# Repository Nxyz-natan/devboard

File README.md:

# devboard
A compact ESP32 development board with onboard 2" ST7789 display, USB-C, LiPo charging via IP5306, GPIO headers, status LEDs, and CH340C for easy programming. Built on the ESP32-WROOM-32 for WiFi and Bluetooth.

my finished pcb

my finished schematics

## Bill of Materials

| Name | Purpose | Qty | Total Cost (USD) | Distributor | Link |
|------|---------|-----|-----------------|-------------|------|
| PCB | PCB | 1 | $1.50 | JLCPCB | - |
| Mini Hotplate | Soldering | 1 | $13.26 | Amazon | - |
| LiPo Battery 1000mAh JST | Battery | 1 | $7.83 | Amazon | - |
| LCSC ST7789 2.0inch Screen | Screen | 1 | $7.67 | LCSC | [link](https://www.lcsc.com/product-detail/C53184555.html) |
| ESP32-WROOM-32-N4 | MCU | 1 | $4.29 | LCSC | [link](https://www.lcsc.com/product-detail/C82899.html) |
| K2-1102SP Push Button | Button | 10 | $0.45 | LCSC | [link](https://www.lcsc.com/product-detail/C127509.html) |
| YLED0402Y LED Yellow | LED | 50 | $0.69 | LCSC | [link](https://www.lcsc.com/product-detail/C20608782.html) |
| EVERLIGHT Green LED | LED | 10 | $0.43 | LCSC | [link](https://www.lcsc.com/product-detail/C74338.html) |
| NATIONSTAR Red LED | LED | 50 | $0.67 | LCSC | [link](https://www.lcsc.com/product-detail/C84256.html) |
| YAGEO 100R 0402 | Resistor | 100 | $0.09 | LCSC | [link](https://www.lcsc.com/product-detail/C106232.html) |
| UNI-ROYAL 1K 0402 | Resistor | 100 | $0.07 | LCSC | [link](https://www.lcsc.com/product-detail/C11702.html) |
| YAGEO 10K 0603 | Resistor | 100 | $0.15 | LCSC | [link](https://www.lcsc.com/product-detail/C98220.html) |
| YAGEO 5.1K 0402 | Resistor | 100 | $0.09 | LCSC | [link](https://www.lcsc.com/product-detail/C105872.html) |
| Samsung 100uF 1206 Cap | Capacitor | 10 | $0.61 | LCSC | [link](https://www.lcsc.com/product-detail/C15008.html) |
| YAGEO 100nF 0402 Cap | Capacitor | 100 | $0.10 | LCSC | [link](https://www.lcsc.com/product-detail/C60474.html) |
| Samsung 10uF 0603 Cap | Capacitor | 50 | $0.40 | LCSC | [link](https://www.lcsc.com/product-detail/C19702.html) |
| Pin Header 1x20 2.54mm | Header | 50 | $0.72 | LCSC | [link](https://www.lcsc.com/product-detail/C50981.html) |
| Pin Header 1x2 2.54mm | Header | 10 | $0.61 | LCSC | [link](https://www.lcsc.com/product-detail/C49661.html) |
| USB-C Receptacle 14P | Connector | 5 | $0.85 | LCSC | [link](https://www.lcsc.com/product-detail/C165948.html) |
| MMBT3904 NPN Transistor | Transistor | 50 | $0.49 | LCSC | [link](https://www.lcsc.com/product-detail/C20526.html) |
| 2N7002 MOSFET | MOSFET | 50 | $0.67 | LCSC | [link](https://www.lcsc.com/product-detail/C8545.html) |
| IP5306 Battery IC | Power | 5 | $1.41 | LCSC | [link](https://www.lcsc.com/product-detail/C181692.html) |
| AMS1117-3.3 LDO | Regulator | 5 | $1.13 | LCSC | [link](https://www.lcsc.com/product-detail/C6186.html) |
| CH340C USB-UART | USB-UART | 1 | $0.58 | LCSC | [link](https://www.lcsc.com/product-detail/C84681.html) |
| JST B2B-PH-K-S(LF)(SN) | JST PH 2.0mm 2pin vertical connector | 20 | $0.67 | LCSC | [link](https://www.lcsc.com/product-detail/C131337.html?s_z=n_JST%2520PH%25202.0mm%25202pin%2520vertical%2520connector&spm=wm.ssy.bg.0.xh&lcsc_vid=ElILAgAEQVUPAgEDTldfUFVVQgMPUQdXRlUMVFMHQVcxVlNRQVBdVFFWQVVdUzsOAxUeFF5JWBYZEEoKFBINSQcJGk4dAgUUFAk%3D) |
soldering paste  soldering   5.09$
soldering tweeters	placing down components	-	$5.89	-	aliexpress

total with shipping and tax: $74.93 usd

finished soldering

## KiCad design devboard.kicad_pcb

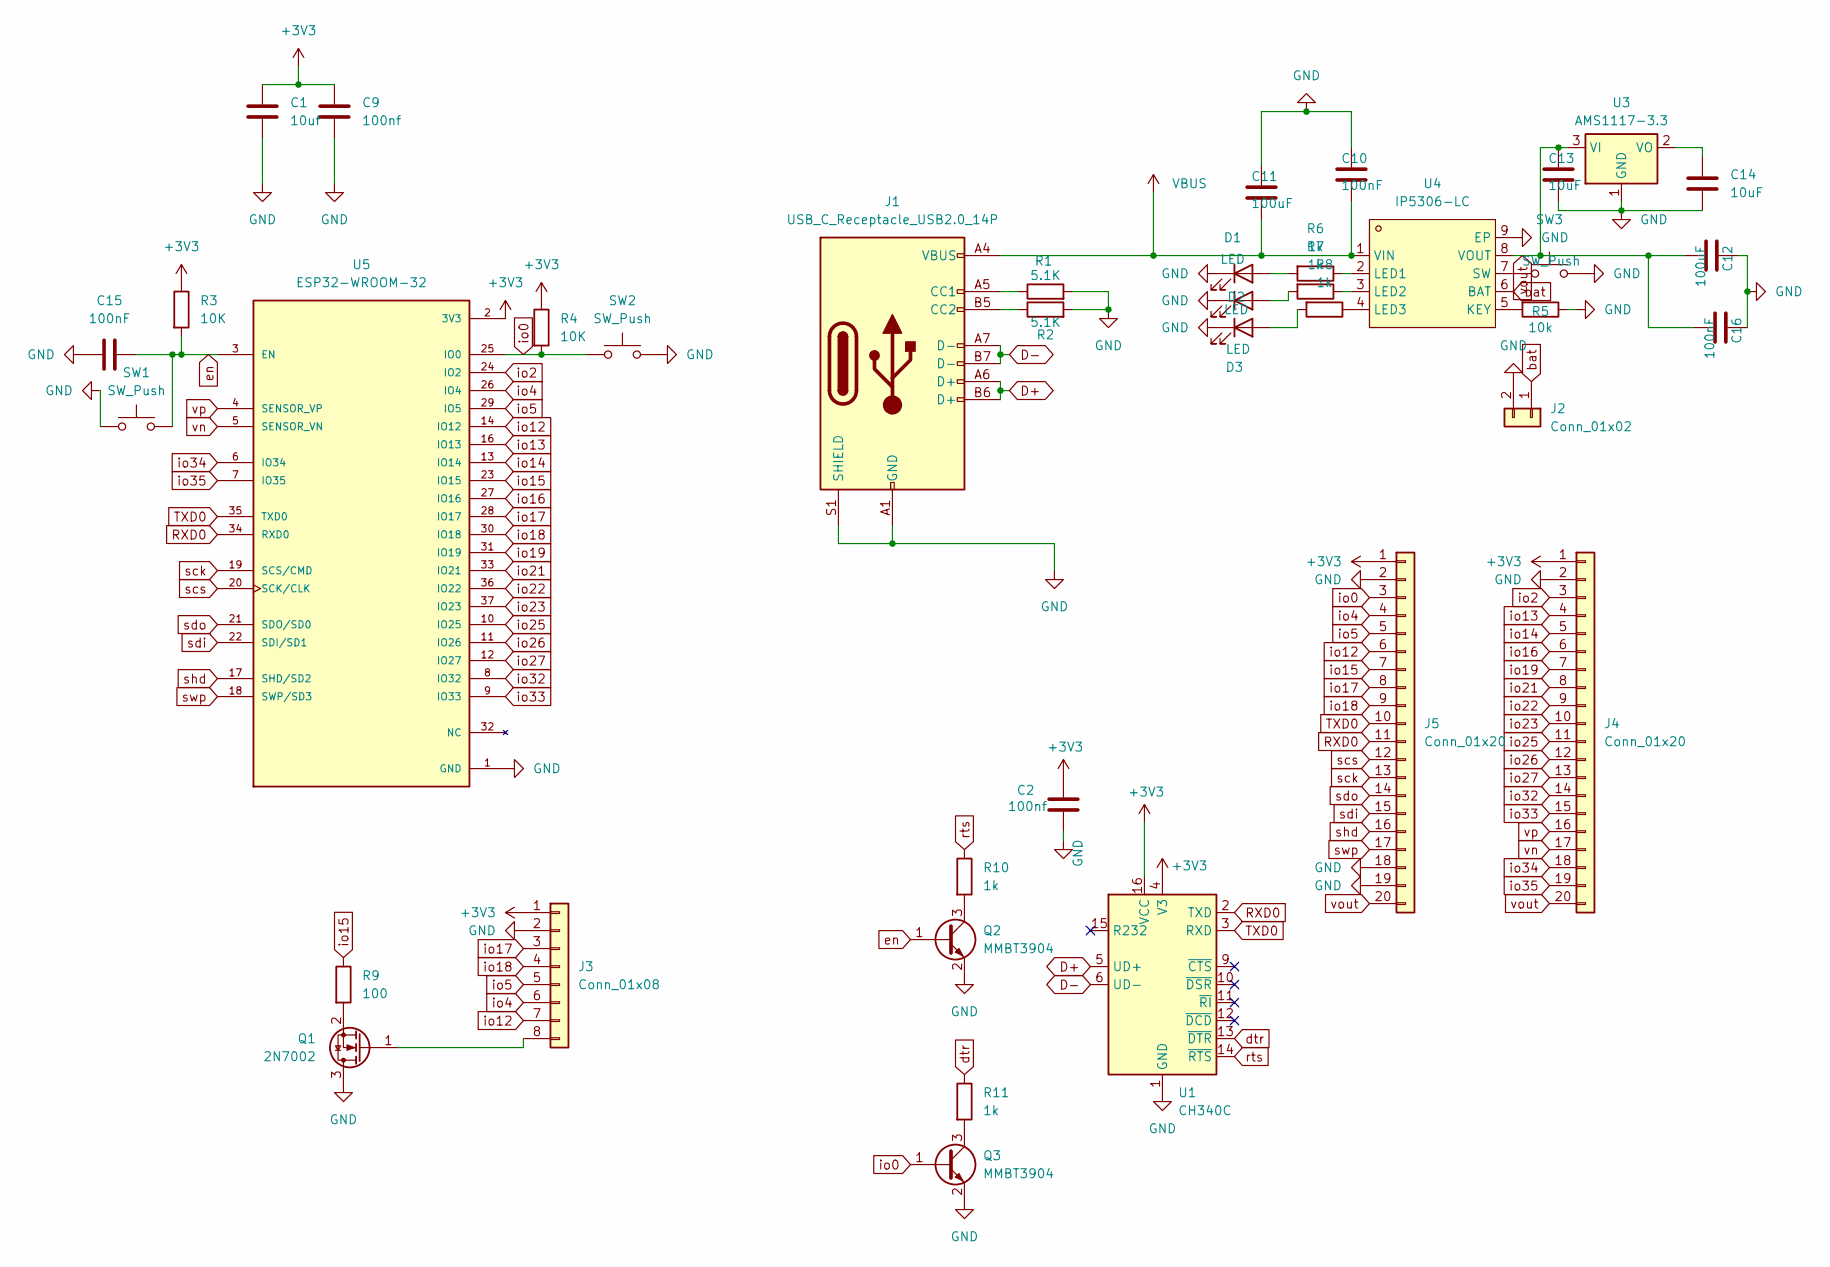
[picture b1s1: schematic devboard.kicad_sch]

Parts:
C1: 10uf; C_0603_1608Metric
C2, C9: 100nf; C_0402_1005Metric
C10, C16: 100nF; C_0603_1608Metric
C11, C12: 100uF; C_1206_3216Metric
C13, C14: 10uF; C_0603_1608Metric
C15: 100nF; C_0402_1005Metric
D1, D2, D3: LED; LED_0402_1005Metric
J1: USB_C_Receptacle_USB2.0_14P; USB_C_Receptacle_HRO_TYPE-C-31-M-12
J2: Conn_01x02; JST_PH_S2B-PH-K_1x02_P2.00mm_Horizontal
J3: Conn_01x08; PinHeader_1x08_P2.54mm_Vertical
J4, J5: Conn_01x20; PinHeader_1x20_P2.54mm_Vertical
Q1: 2N7002; SOT-23
Q2, Q3: MMBT3904; SOT-23
R1, R2: 5.1K; R_0402_1005Metric
R3, R4: 10K; R_0402_1005Metric
R5: 10k; R_0402_1005Metric
R6, R7, R8, R10, R11: 1k; R_0402_1005Metric
R9: 100; R_0402_1005Metric
SW1, SW2, SW3: SW_Push; SW_SPST_TL3342
U1: CH340C; SOIC-16_3.9x9.9mm_P1.27mm
U3: AMS1117-3.3; SOT-223-3_TabPin2
U4: IP5306-LC; ESOP-8_L4.9-W3.9-P1.27-LS6.0-BL-EP; MPN IP5306-LC; LCSC Part C605440
U5: ESP32-WROOM-32; MODULE_ESP32-WROOM-32; PARTREV 2.9

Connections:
+3V3: C1.1, C2.1, C9.1, J3.1, J4.1, J5.1, R3.1, R4.1, U1.4 (V3), U1.16 (VCC), U5.2 (3V3)
D+: J1.A6 (D+), J1.B6 (D+), U1.5 (UD+)
D-: J1.A7 (D-), J1.B7 (D-), U1.6 (UD-)
GND: C1.2, C2.2, C9.2, C10.1, C11.1, C12.1, C13.2, C14.2, C15.1, C16.1, D1.1 (K), D2.1 (K), D3.1 (K), J1.A1 (GND), J1.A12 (GND), J1.B1 (GND), J1.B12 (GND), J1.S1 (SHIELD), J2.2, J3.2, J4.2, J5.2, J5.18, J5.19, Q1.3 (D), Q2.2 (E), Q3.2 (E), R1.2, R2.2, R5.1, SW1.1, SW2.2, SW3.2, U1.1 (GND), U3.1 (GND), U4.9 (EP), U5.1 (GND), U5.15 (GND), U5.38 (GND), U5.39_1 (GND), U5.39_2 (GND), U5.39_3 (GND), U5.39_4 (GND), U5.39_5 (GND), U5.39_6 (GND), U5.39_7 (GND), U5.39_8 (GND), U5.39_9 (GND), U5.39_10 (GND), U5.39_11 (GND), U5.39_12 (GND), U5.39_13 (GND), U5.39_14 (GND), U5.39_15 (GND), U5.39_16 (GND), U5.39_17 (GND), U5.39_18 (GND), U5.39_19 (GND), U5.39_20 (GND), U5.39_21 (GND)
unnamed: D1.2 (A), R6.2
unnamed: D2.2 (A), R7.2
unnamed: D3.2 (A), R8.2
unnamed: J1.A5 (CC1), R1.1
unnamed: J1.B5 (CC2), R2.1
unnamed: J3.8, Q1.1 (G)
unnamed: Q1.2 (S), R9.2
unnamed: Q2.3 (C), R10.2
unnamed: Q3.3 (C), R11.2
unnamed: C14.1, U3.2 (VO)
unnamed: R5.2, U4.5 (KEY)
unnamed: R6.1, U4.2 (LED1)
unnamed: R7.1, U4.3 (LED2)
unnamed: R8.1, U4.4 (LED3)
unnamed: SW3.1, U4.7 (SW)
RXD0: J5.11, U1.2 (TXD), U5.34 (RXD0)
TXD0: J5.10, U1.3 (RXD), U5.35 (TXD0)
VBUS: C10.2, C11.2, J1.A4 (VBUS), J1.A9 (VBUS), J1.B4 (VBUS), J1.B9 (VBUS), U4.1 (VIN)
bat: J2.1, U4.6 (BAT)
dtr: R11.1, U1.13 (~DTR)
en: C15.2, Q2.1 (B), R3.2, SW1.2, U5.3 (EN)
io0: J5.3, Q3.1 (B), R4.2, SW2.1, U5.25 (IO0)
io2: J4.3, U5.24 (IO2)
io4: J3.6, J5.4, U5.26 (IO4)
io5: J3.5, J5.5, U5.29 (IO5)
io12: J3.7, J5.6, U5.14 (IO12)
io13: J4.4, U5.16 (IO13)
io14: J4.5, U5.13 (IO14)
io15: J5.7, R9.1, U5.23 (IO15)
io16: J4.6, U5.27 (IO16)
io17: J3.3, J5.8, U5.28 (IO17)
io18: J3.4, J5.9, U5.30 (IO18)
io19: J4.7, U5.31 (IO19)
io21: J4.8, U5.33 (IO21)
io22: J4.9, U5.36 (IO22)
io23: J4.10, U5.37 (IO23)
io25: J4.11, U5.10 (IO25)
io26: J4.12, U5.11 (IO26)
io27: J4.13, U5.12 (IO27)
io32: J4.14, U5.8 (IO32)
io33: J4.15, U5.9 (IO33)
io34: J4.18, U5.6 (IO34)
io35: J4.19, U5.7 (IO35)
rts: R10.1, U1.14 (~RTS)
sck: J5.13, U5.19 (SCS/CMD)
scs: J5.12, U5.20 (SCK/CLK)
sdi: J5.15, U5.22 (SDI/SD1)
sdo: J5.14, U5.21 (SDO/SD0)
shd: J5.16, U5.17 (SHD/SD2)
swp: J5.17, U5.18 (SWP/SD3)
vn: J4.17, U5.5 (SENSOR_VN)
vout: C12.2, C13.1, C16.2, J4.20, J5.20, U3.3 (VI), U4.8 (VOUT)
vp: J4.16, U5.4 (SENSOR_VP)

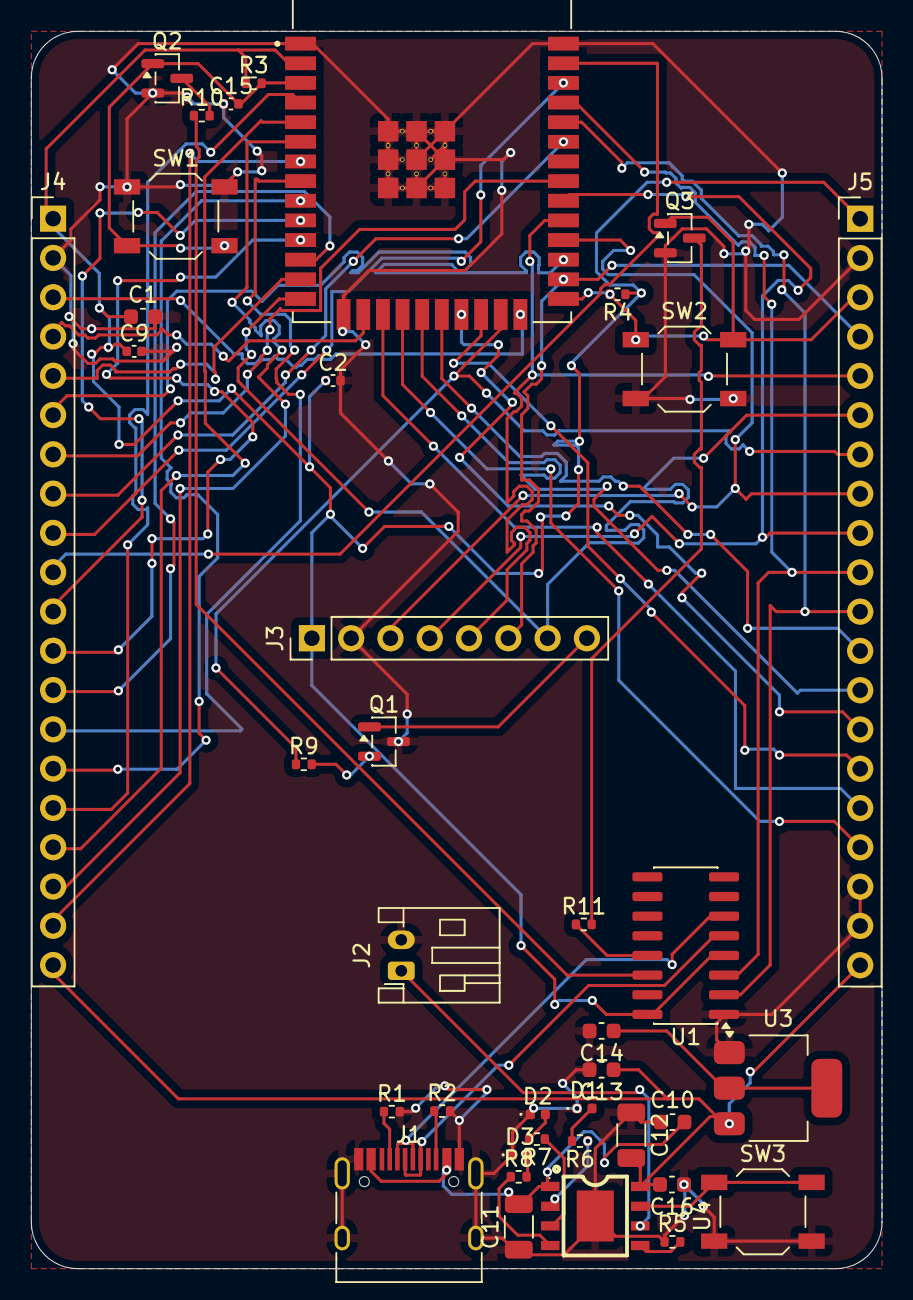
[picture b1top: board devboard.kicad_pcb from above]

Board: 2 copper layers, 55.0 x 80.0 mm, 39 parts (0 on the bottom side), 57 nets.

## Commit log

2026-04-13 Create pcb
2026-06-28 Add image of finished soldering project
    Added an image of the finished soldering project.
